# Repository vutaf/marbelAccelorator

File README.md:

# marbelAccelorator
Based on: https://www.instructables.com/Electromagnetic-Marble-Accelerator-for-Gravitrax/

## WIP

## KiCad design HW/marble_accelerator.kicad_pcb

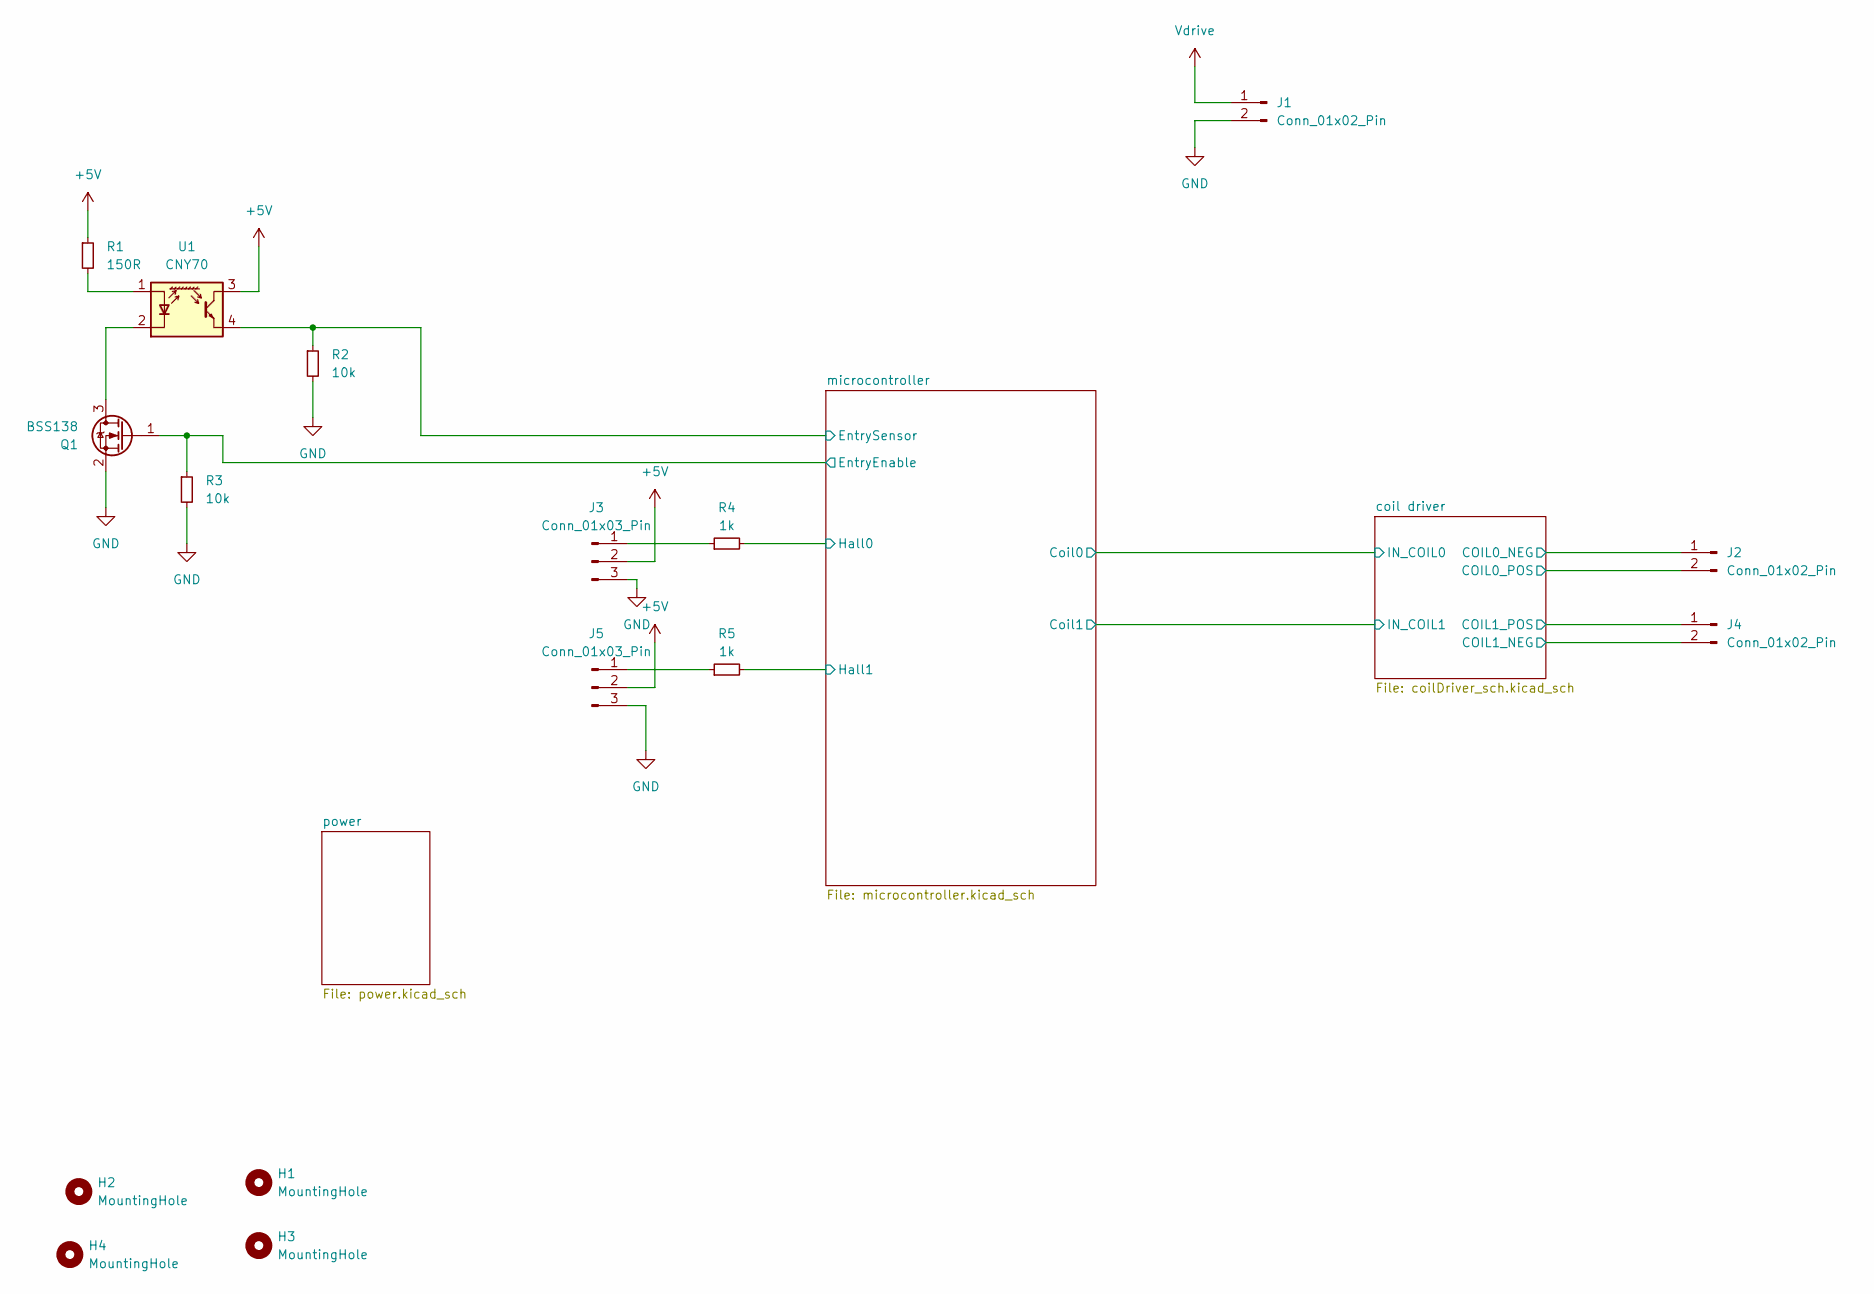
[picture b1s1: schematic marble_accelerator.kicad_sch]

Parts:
H1, H2, H3, H4: MountingHole; MountingHole_3.2mm_M3
J1, J2, J4: Conn_01x02_Pin; TerminalBlock_MetzConnect_Type059_RT06302HBWC_1x02_P3.50mm_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
J3, J5: Conn_01x03_Pin; JST_XH_B3B-XH-A_1x03_P2.50mm_Vertical
Q1: BSS138; SOT-23
R1: 150R; C_0603_1608Metric_Pad1.08x0.95mm_HandSolder
R2, R3: 10k; C_0603_1608Metric_Pad1.08x0.95mm_HandSolder
R4, R5: 1k; C_0603_1608Metric_Pad1.08x0.95mm_HandSolder
U1: CNY70; Vishay_CNY70

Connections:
+5V: J3.2, J5.2, R1.1, U1.3 (C); also elsewhere on the board
/coil driver/COIL0_NEG: J2.1; also elsewhere on the board
/coil driver/COIL1_NEG: J4.2; also elsewhere on the board
/microcontroller/EntryEnable: Q1.1 (G), R3.1; also elsewhere on the board
/microcontroller/EntrySensor: R2.1, U1.4 (E); also elsewhere on the board
/microcontroller/Hall0: R4.2; also elsewhere on the board
/microcontroller/Hall1: R5.2; also elsewhere on the board
GND: J1.2, J3.3, J5.3, Q1.2 (S), R2.2, R3.2; also elsewhere on the board
unnamed: J3.1, R4.1
unnamed: J5.1, R5.1
unnamed: Q1.3 (D), U1.2 (K)
unnamed: R1.2, U1.1 (A)
Vdrive: J1.1, J2.2, J4.1; also elsewhere on the board

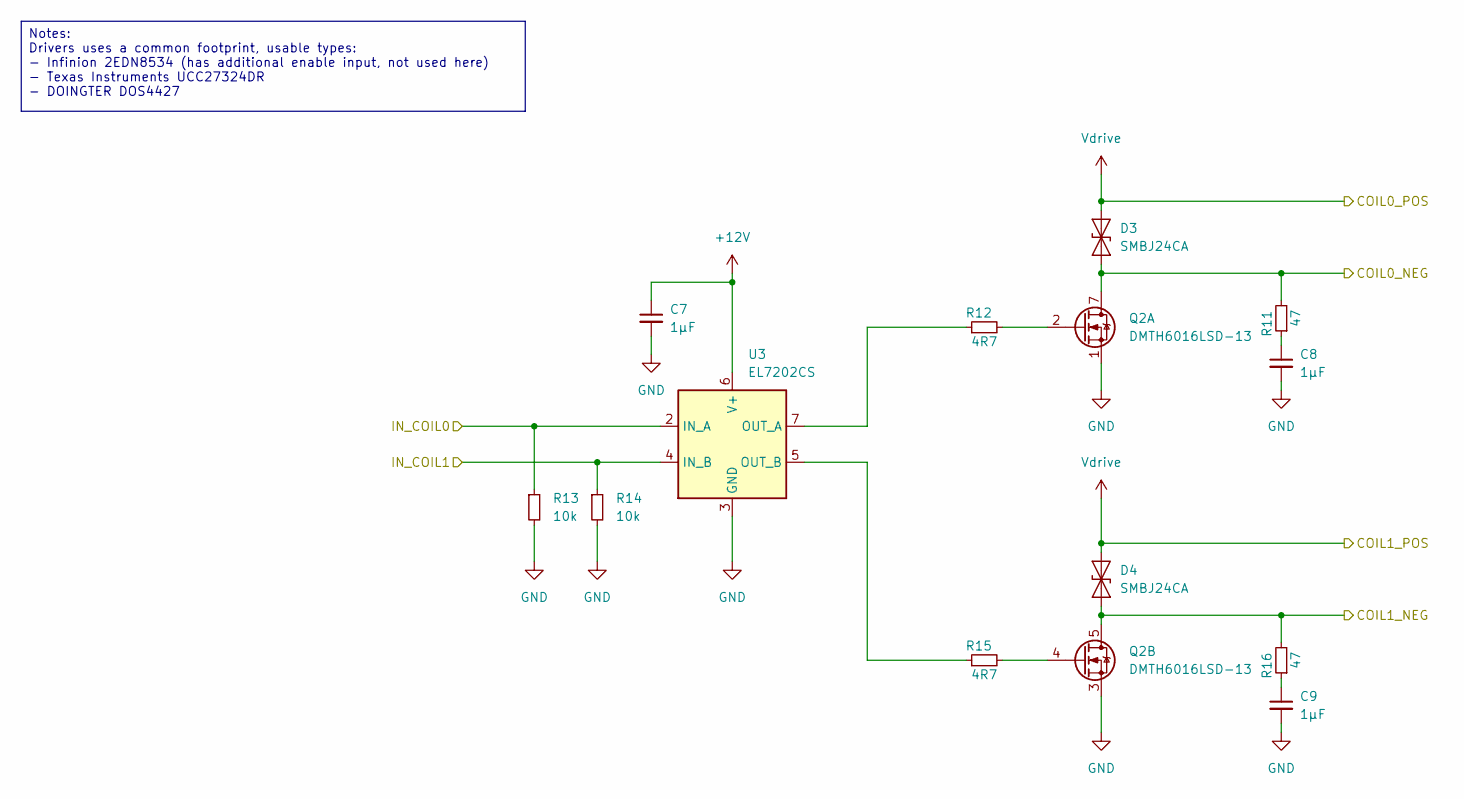
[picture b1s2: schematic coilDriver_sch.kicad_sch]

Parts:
C7: 1µF; C_0805_2012Metric_Pad1.18x1.45mm_HandSolder
C8, C9: 1µF; C_1210_3225Metric_Pad1.33x2.70mm_HandSolder
D3, D4: SMBJ24CA; D_SMB
Q2: DMTH6016LSD-13; SOIC-8_3.9x4.9mm_P1.27mm
R11, R16: 47; R_1206_3216Metric_Pad1.30x1.75mm_HandSolder
R12, R15: 4R7; R_0603_1608Metric_Pad0.98x0.95mm_HandSolder
R13, R14: 10k; R_0603_1608Metric_Pad0.98x0.95mm_HandSolder
U3: EL7202CS; SOIC-8_3.9x4.9mm_P1.27mm

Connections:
+12V: C7.1, U3.6 (V+); also elsewhere on the board
/coil driver/COIL0_NEG: D3.1 (A1), Q2.7 (D1), Q2.8 (D1), R11.2; also elsewhere on the board
/coil driver/COIL1_NEG: D4.1 (A1), Q2.5 (D2), Q2.6 (D2), R16.2; also elsewhere on the board
/coil driver/IN_COIL0: R13.1, U3.2 (IN_A); also elsewhere on the board
/coil driver/IN_COIL1: R14.1, U3.4 (IN_B); also elsewhere on the board
GND: C7.2, C8.2, C9.2, Q2.1 (S1), Q2.3 (S2), R13.2, R14.2, U3.3 (GND); also elsewhere on the board
unnamed: C8.1, R11.1
unnamed: C9.1, R16.1
unnamed: Q2.2 (G1), R12.2
unnamed: Q2.4 (G2), R15.2
unnamed: R12.1, U3.7 (OUT_A)
unnamed: R15.1, U3.5 (OUT_B)
Vdrive: D3.2 (A2), D4.2 (A2); also elsewhere on the board

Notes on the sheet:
Notes: Drivers uses a common footprint, usable types: - Infinion 2EDN8534 (has additional enable input, not used here) - Texas Instruments UCC27324DR - DOINGTER DOS4427

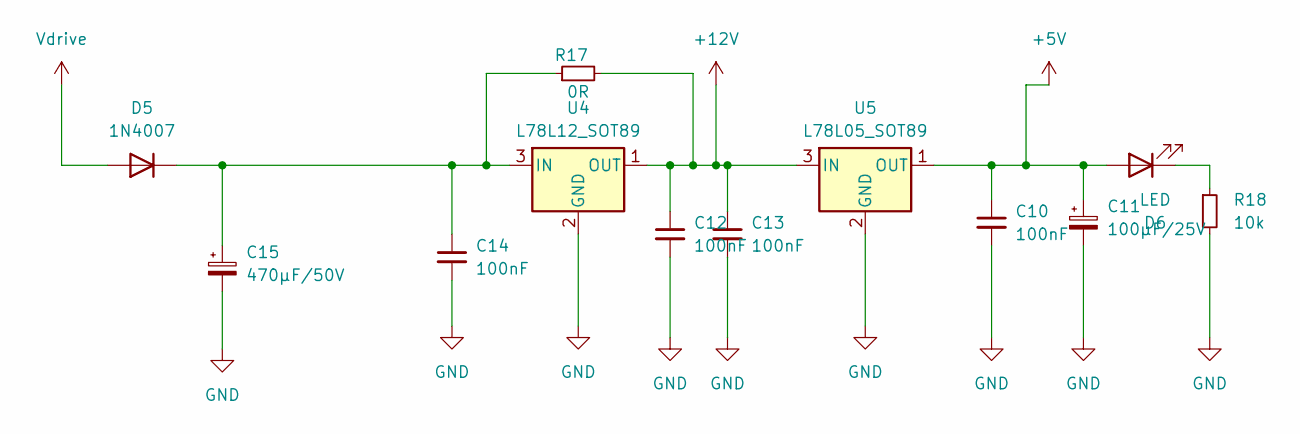
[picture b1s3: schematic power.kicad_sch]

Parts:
C10, C12, C13, C14: 100nF; C_0603_1608Metric_Pad1.08x0.95mm_HandSolder
C11: 100µF/25V; CP_Radial_D6.3mm_P2.50mm
C15: 470µF/50V; CP_Radial_D13.0mm_P5.00mm
D5: 1N4007; R_MELF_MMB-0207
D6: LED; LED_PLCC-2_3.4x3.0mm_KA
R17: 0R; R_0603_1608Metric_Pad0.98x0.95mm_HandSolder
R18: 10k; R_0603_1608Metric_Pad0.98x0.95mm_HandSolder
U4: L78L12_SOT89; SOT-89-3
U5: L78L05_SOT89; SOT-89-3

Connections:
+5V: C10.1, C11.1, D6.2 (A), U5.1 (OUT); also elsewhere on the board
+12V: C12.1, C13.1, R17.2, U4.1 (OUT), U5.3 (IN); also elsewhere on the board
GND: C10.2, C11.2, C12.2, C13.2, C14.2, C15.2, R18.2, U4.2 (GND), U5.2 (GND); also elsewhere on the board
unnamed: C14.1, C15.1, D5.1 (K), R17.1, U4.3 (IN)
unnamed: D6.1 (K), R18.1
Vdrive: D5.2 (A); also elsewhere on the board

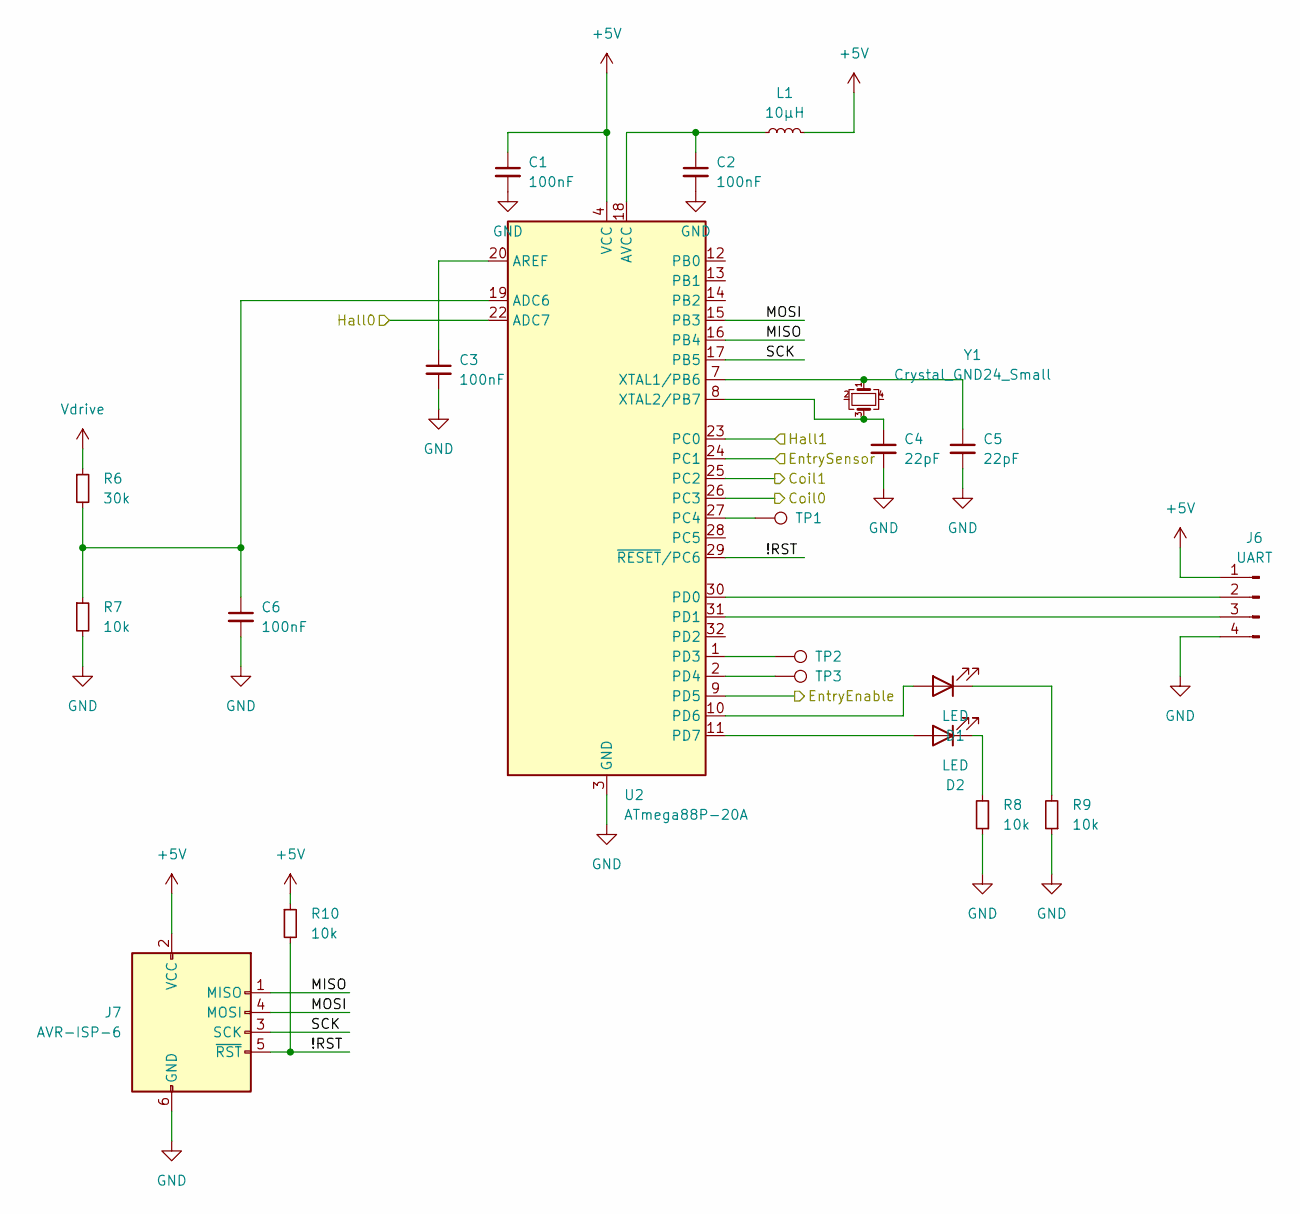
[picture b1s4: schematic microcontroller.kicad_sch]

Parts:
C1, C2, C3, C6: 100nF; C_0603_1608Metric_Pad1.08x0.95mm_HandSolder
C4, C5: 22pF; C_0603_1608Metric_Pad1.08x0.95mm_HandSolder
D1, D2: LED; LED_PLCC-2_3.4x3.0mm_KA
J6: UART; PinHeader_1x04_P2.54mm_Vertical
J7: AVR-ISP-6; PinHeader_2x03_P2.54mm_Vertical
L1: 10µH; L_0603_1608Metric_Pad1.05x0.95mm_HandSolder
R6: 30k; R_0603_1608Metric_Pad0.98x0.95mm_HandSolder
R7, R8, R9, R10: 10k; R_0603_1608Metric_Pad0.98x0.95mm_HandSolder
TP1, TP2, TP3: TestPoint; TestPoint_Pad_D2.0mm
U2: ATmega88P-20A; TQFP-32_7x7mm_P0.8mm
Y1: Crystal_GND24_Small; Crystal_SMD_3225-4Pin_3.2x2.5mm_HandSoldering

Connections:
+5V: C1.1, J6.1, J7.2 (VCC), L1.2, R10.1, U2.4 (VCC), U2.6 (VCC); also elsewhere on the board
/coil driver/IN_COIL0: U2.26 (PC3); also elsewhere on the board
/coil driver/IN_COIL1: U2.25 (PC2); also elsewhere on the board
/microcontroller/!RST: J7.5 (~RST), R10.2, U2.29 (~RESET/PC6)
/microcontroller/EntryEnable: U2.9 (PD5); also elsewhere on the board
/microcontroller/EntrySensor: U2.24 (PC1); also elsewhere on the board
/microcontroller/Hall0: U2.22 (ADC7); also elsewhere on the board
/microcontroller/Hall1: U2.23 (PC0); also elsewhere on the board
/microcontroller/MISO: J7.1 (MISO), U2.16 (PB4)
/microcontroller/MOSI: J7.4 (MOSI), U2.15 (PB3)
/microcontroller/SCK: J7.3 (SCK), U2.17 (PB5)
GND: C1.2, C2.2, C3.2, C4.2, C5.2, C6.2, J6.4, J7.6 (GND), R7.2, R8.1, R9.1, U2.3 (GND), U2.5 (GND), U2.21 (GND); also elsewhere on the board
unnamed: D1.2 (A), U2.10 (PD6)
unnamed: D1.1 (K), R9.2
unnamed: D2.2 (A), U2.11 (PD7)
unnamed: D2.1 (K), R8.2
unnamed: J6.2, U2.30 (PD0)
unnamed: J6.3, U2.31 (PD1)
unnamed: C6.1, R6.2, R7.1, U2.19 (ADC6)
unnamed: C3.1, U2.20 (AREF)
unnamed: C2.1, L1.1, U2.18 (AVCC)
unnamed: TP1.1, U2.27 (PC4)
unnamed: TP2.1, U2.1 (PD3)
unnamed: TP3.1, U2.2 (PD4)
unnamed: C5.1, U2.7 (XTAL1/PB6), Y1.1
unnamed: C4.1, U2.8 (XTAL2/PB7), Y1.3
Vdrive: R6.1; also elsewhere on the board

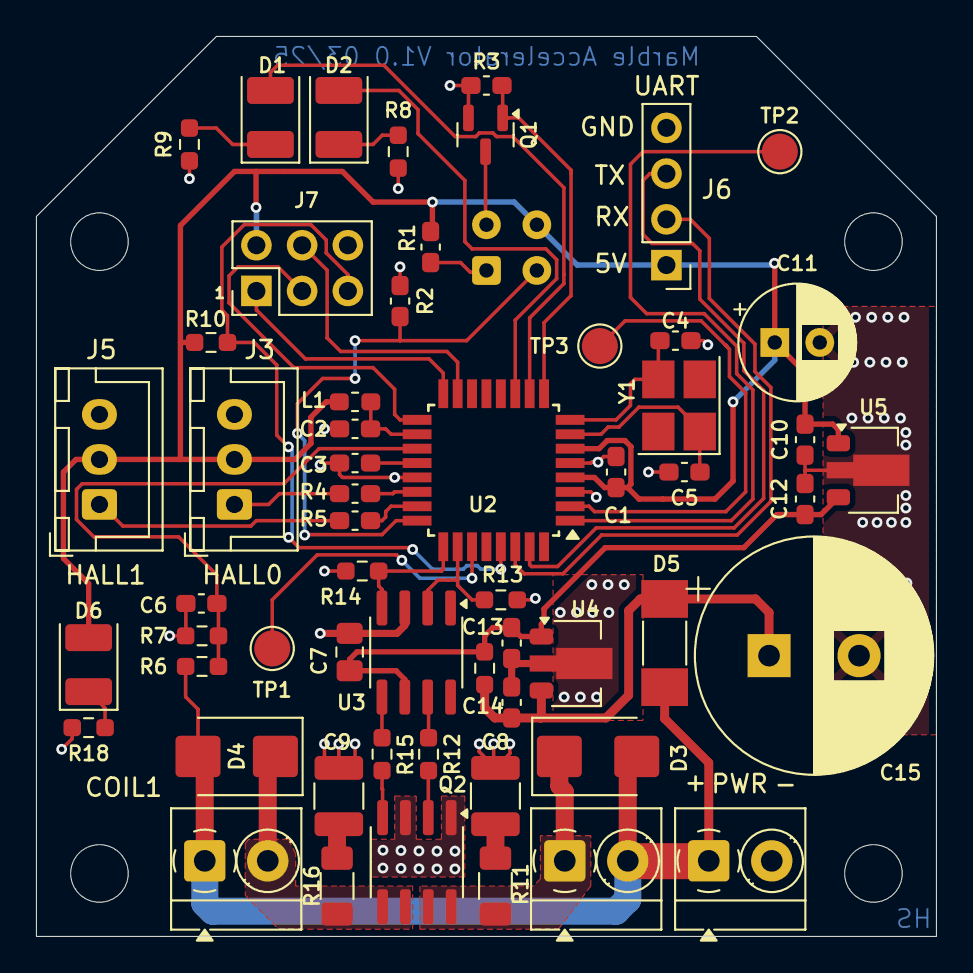
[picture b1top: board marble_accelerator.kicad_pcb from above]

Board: 2 copper layers, 50.0 x 50.0 mm, 62 parts (1 on the bottom side), 42 nets.

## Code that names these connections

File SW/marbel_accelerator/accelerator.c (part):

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
/*
 * Config: Hallsensor 0 on ADC7 (no GPIO)
 *         Hallsensor 1 on PC0
 *         CNY70 on PC1
 *         CNY70 enable on PD5 (COM0B)
 *         switch on PC0    -> removed
 *         led1 on PD6
 *         led2 on PD7
 *         coil 0 on PC3
 *         coil 1 on PC2
 *         debug pin on PD3
 *         debug pin2 on PD4
*/
#include <avr/interrupt.h>
#include <stddef.h>
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    //set hall sensor 0 pin is only analog, so nothing to do

    DDRC &= ~(1<<PINC0);    //set hall sensor 1 pin to input (should be default)
    DIDR0 |= (1<<ADC0D);    //deactivate digital buffer on PC0

    DDRC &= ~(1<<PINC1);    //set CNY70 pin to input (should be default)
    DIDR0 |= (1<<ADC1D);    //deactivate digital buffer on PC1

    initAcceleratorTimer();

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
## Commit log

2025-03-09 add hw
2025-03-11 initial commit of SW
2025-03-11 add sourceproject to readme
2025-03-13 update schematic
2025-03-15 update HW, reduce board to 5x5 cm
2025-03-18 update HW
2025-03-23 update layout
2025-03-25 update layout and schematic
2025-03-25 update schematic and board
2025-03-25 add WIP to readme
2025-03-27 finished first layout
2025-03-29 first HW order state
2025-03-29 cosmetic changes on layout
2025-04-23 rework to use the new hardware with Mega88a on it
